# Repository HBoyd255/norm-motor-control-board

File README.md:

# N.O.R.M. Motor Control Board <br> (Neat Omnidirectional Robotic Module)

<!-- Harry Boyd - 30/10/2024 - github.com/hboyd255 -->

This is a board that controls the motors on Project N.O.R.M. It uses an arduino
nano 33 BLE as the controller.

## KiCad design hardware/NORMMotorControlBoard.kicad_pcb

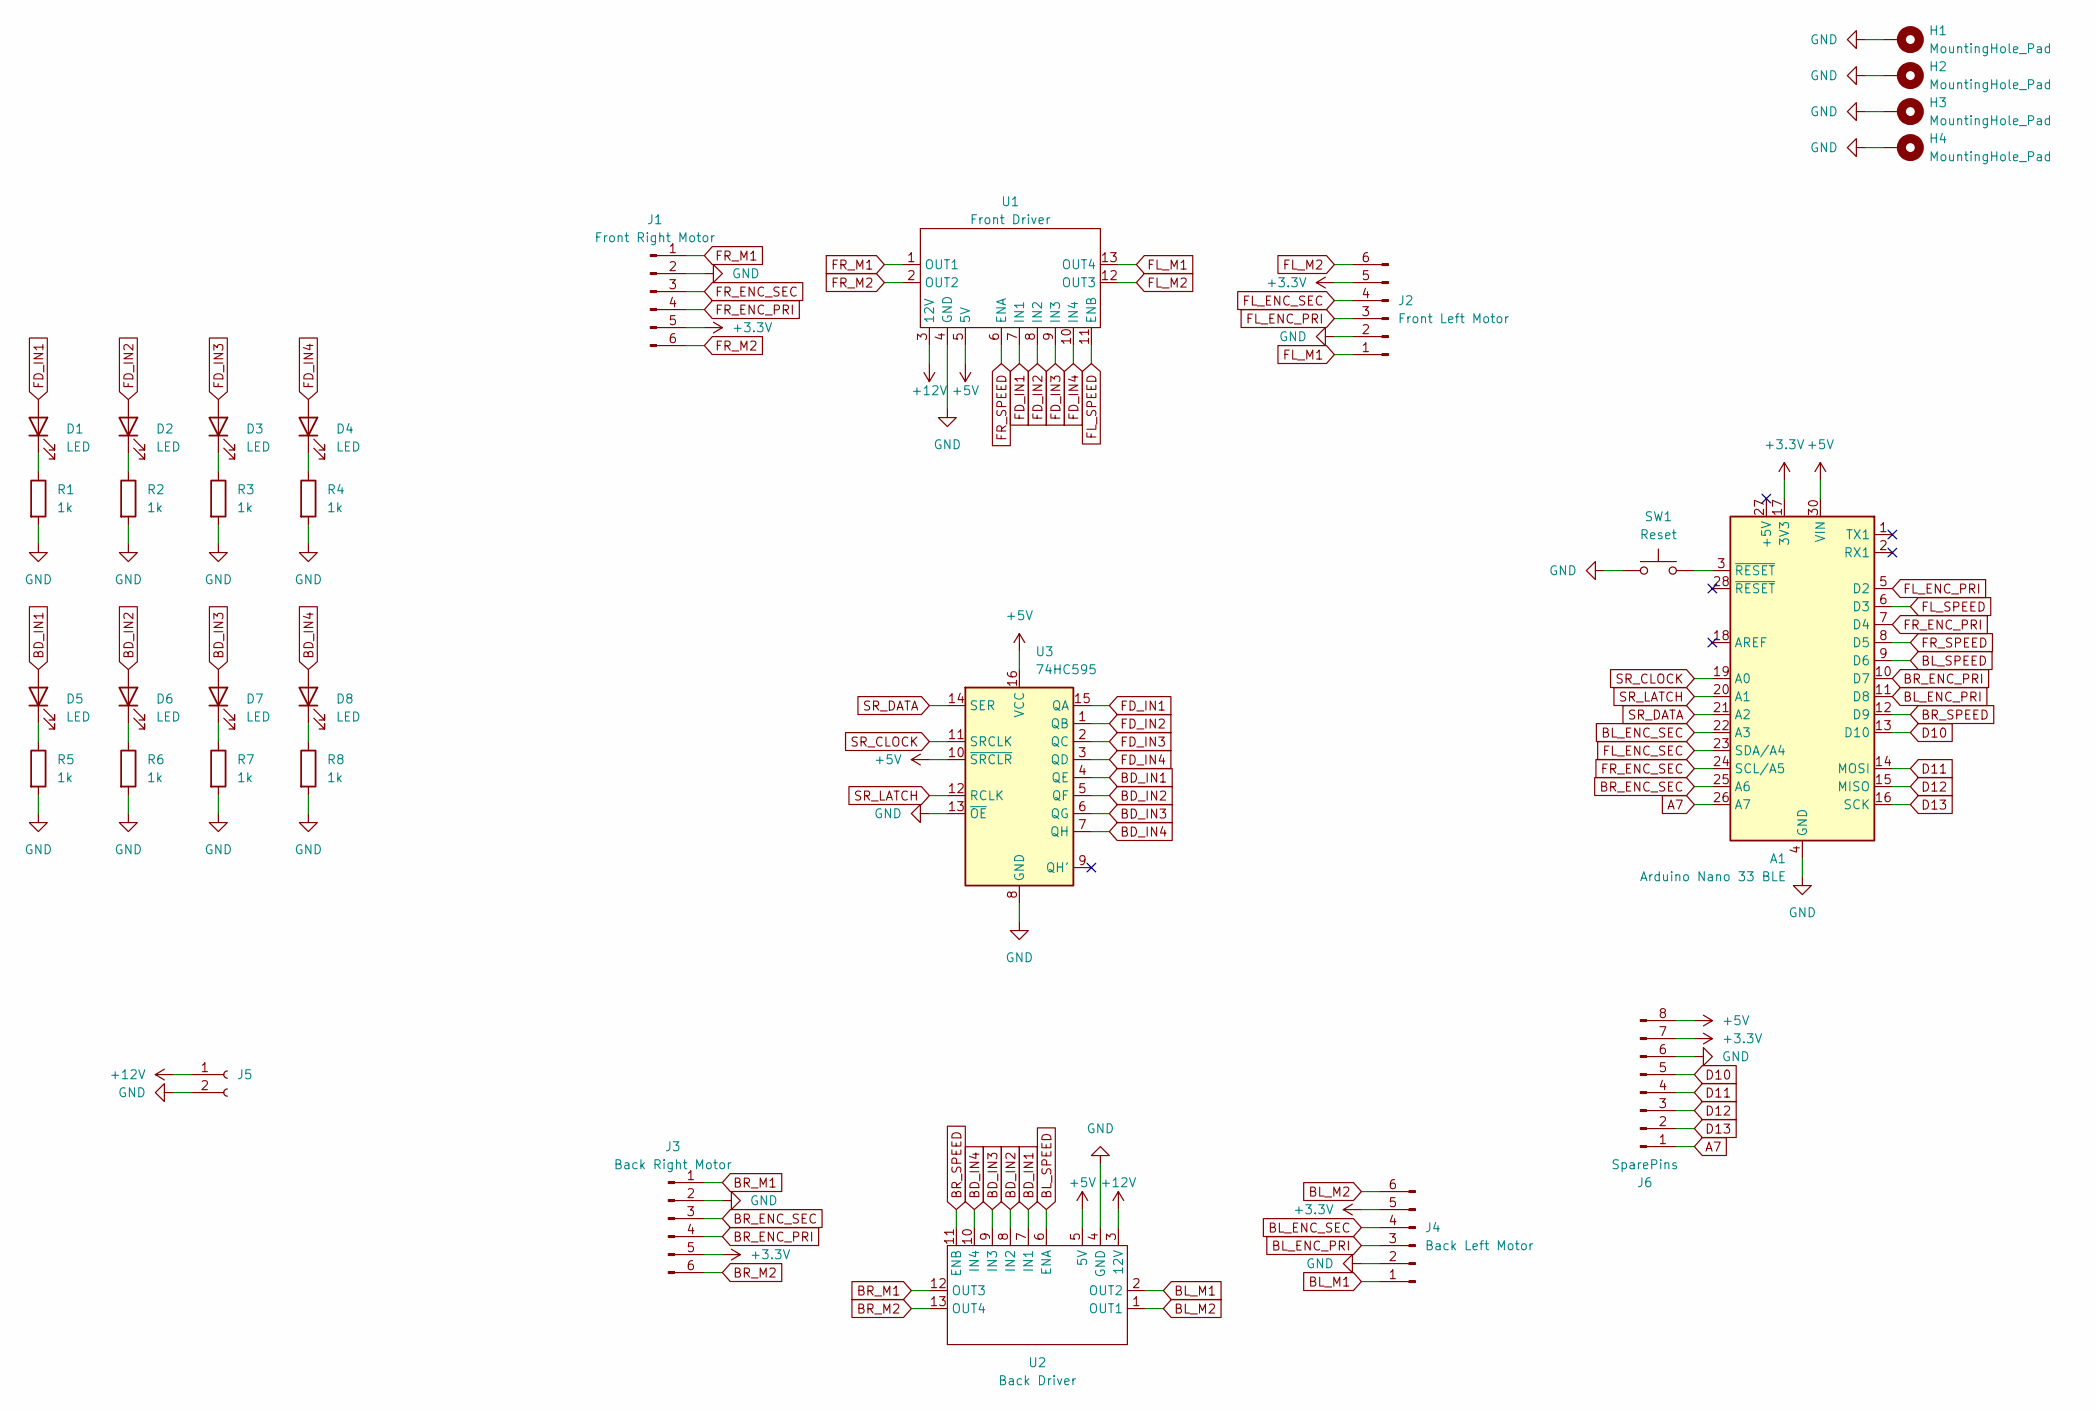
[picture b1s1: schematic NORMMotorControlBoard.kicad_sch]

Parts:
A1: Arduino Nano 33 BLE; Arduino_Nano
D1, D2, D3, D4, D5, D6, D7, D8: LED; LED_0603_1608Metric
H1, H2, H3, H4: MountingHole_Pad; MountingHole_2.7mm_M2.5_Pad
J1: Front Right Motor; JST_PH_S6B-PH-K_1x06_P2.00mm_Horizontal
J2: Front Left Motor; JST_PH_S6B-PH-K_1x06_P2.00mm_Horizontal
J3: Back Right Motor; JST_PH_S6B-PH-K_1x06_P2.00mm_Horizontal
J4: Back Left Motor; JST_PH_S6B-PH-K_1x06_P2.00mm_Horizontal
J5: Conn_01x02_Socket; Samtec_HPM-02-01-x-S_Straight_1x02_Pitch5.08mm
J6: SparePins; PinHeader_1x08_P2.54mm_Horizontal
R1, R2, R3, R4, R5, R6, R7, R8: 1k; R_0603_1608Metric
SW1: Reset; Two_Pin_Through_Hole_Push_Button
U1: Front Driver; L298N
U2: Back Driver; L298N
U3: 74HC595; DIP-16_W7.62mm

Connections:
+3.3V: A1.17 (3V3), J1.5, J2.5, J3.5, J4.5, J6.7
+5V: A1.30 (VIN), J6.8, U1.5 (5V), U2.5 (5V), U3.10 (~SRCLR), U3.16 (VCC)
+12V: J5.1, U1.3 (12V), U2.3 (12V)
A7: A1.26 (A7), J6.1
BD_IN1: D5.2 (A), U2.7 (IN1), U3.4 (QE)
BD_IN2: D6.2 (A), U2.8 (IN2), U3.5 (QF)
BD_IN3: D7.2 (A), U2.9 (IN3), U3.6 (QG)
BD_IN4: D8.2 (A), U2.10 (IN4), U3.7 (QH)
BL_ENC_PRI: A1.11 (D8), J4.3
BL_ENC_SEC: A1.22 (A3), J4.4
BL_M1: J4.1, U2.2 (OUT2)
BL_M2: J4.6, U2.1 (OUT1)
BL_SPEED: A1.9 (D6), U2.6 (ENA)
BR_ENC_PRI: A1.10 (D7), J3.4
BR_ENC_SEC: A1.25 (A6), J3.3
BR_M1: J3.1, U2.12 (OUT3)
BR_M2: J3.6, U2.13 (OUT4)
BR_SPEED: A1.12 (D9), U2.11 (ENB)
D10: A1.13 (D10), J6.5
D11: A1.14 (MOSI), J6.4
D12: A1.15 (MISO), J6.3
D13: A1.16 (SCK), J6.2
FD_IN1: D1.2 (A), U1.7 (IN1), U3.15 (QA)
FD_IN2: D2.2 (A), U1.8 (IN2), U3.1 (QB)
FD_IN3: D3.2 (A), U1.9 (IN3), U3.2 (QC)
FD_IN4: D4.2 (A), U1.10 (IN4), U3.3 (QD)
FL_ENC_PRI: A1.5 (D2), J2.3
FL_ENC_SEC: A1.23 (SDA/A4), J2.4
FL_M1: J2.1, U1.13 (OUT4)
FL_M2: J2.6, U1.12 (OUT3)
FL_SPEED: A1.6 (D3), U1.11 (ENB)
FR_ENC_PRI: A1.7 (D4), J1.4
FR_ENC_SEC: A1.24 (SCL/A5), J1.3
FR_M1: J1.1, U1.1 (OUT1)
FR_M2: J1.6, U1.2 (OUT2)
FR_SPEED: A1.8 (D5), U1.6 (ENA)
GND: A1.4 (GND), A1.29 (GND), H1.1, H2.1, H3.1, H4.1, J1.2, J2.2, J3.2, J4.2, J5.2, J6.6, R1.2, R2.2, R3.2, R4.2, R5.2, R6.2, R7.2, R8.2, SW1.1, U1.4 (GND), U2.4 (GND), U3.8 (GND), U3.13 (~OE)
unnamed: A1.3 (~RESET), SW1.2
unnamed: D1.1 (K), R1.1
unnamed: D2.1 (K), R2.1
unnamed: D3.1 (K), R3.1
unnamed: D4.1 (K), R4.1
unnamed: D5.1 (K), R5.1
unnamed: D6.1 (K), R6.1
unnamed: D7.1 (K), R7.1
unnamed: D8.1 (K), R8.1
SR_CLOCK: A1.19 (A0), U3.11 (SRCLK)
SR_DATA: A1.21 (A2), U3.14 (SER)
SR_LATCH: A1.20 (A1), U3.12 (RCLK)

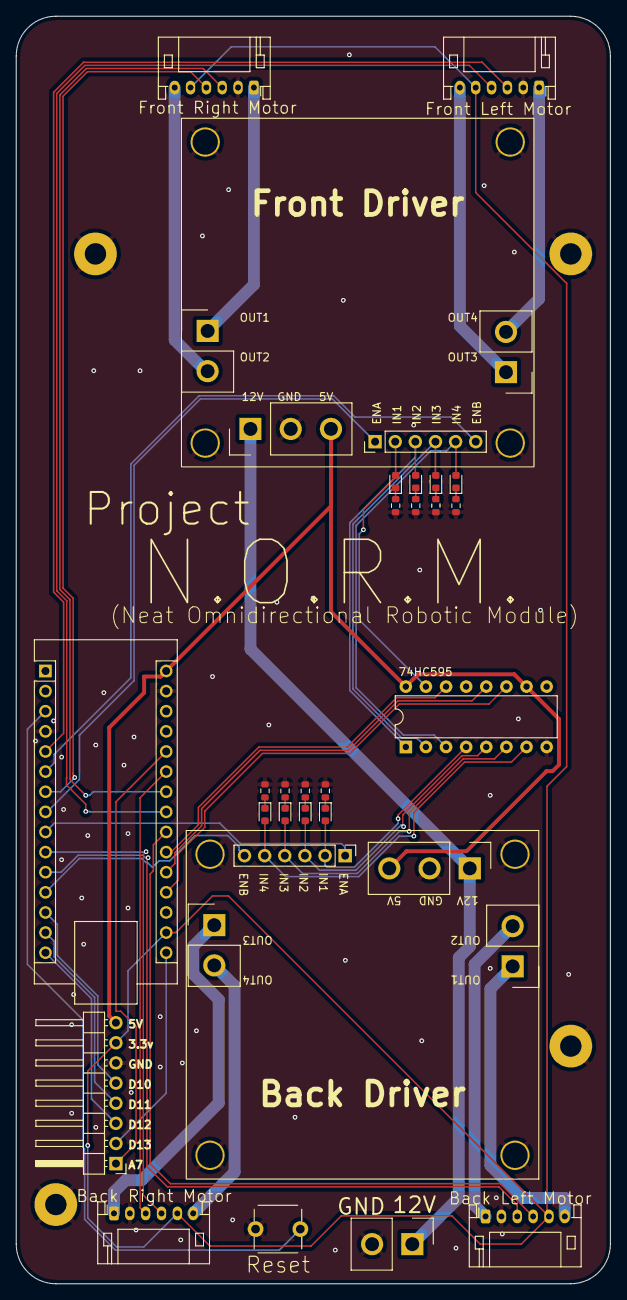
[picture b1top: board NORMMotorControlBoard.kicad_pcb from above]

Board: 2 copper layers, 75.0 x 160.0 mm, 31 parts (0 on the bottom side), 49 nets.

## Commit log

2024-10-30 Created repo
2024-10-30 Added local 3d files for render
2024-10-30 Connected nets to arduino
2024-10-30 Finished schematic and placed components
2024-10-30 Finished V1.0
2024-11-20 Added USB C and replaced components
2024-11-20 renamed motor board
2024-11-20 Exported board v1.1
2025-02-15 Removed license until further notice
2025-02-15 Created symbol for L298N
2025-02-15 Finished schematic for V1.3
2025-02-17 Layout parts for L298N footprint
2025-02-17 Wired up pins of L298N footprint
2025-02-17 Finished schematic for V1.2
2025-02-17 Placed components
2025-02-17 V1.3
